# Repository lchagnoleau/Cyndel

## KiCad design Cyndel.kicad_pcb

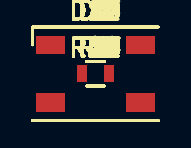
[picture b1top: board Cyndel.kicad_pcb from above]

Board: 2 copper layers, 80 parts (0 on the bottom side), 91 nets, no tracks yet.

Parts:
D1, D2, D3, D4, D5, D6, D7, D8, D9, D10, D11, D12, D13, D14, D15, D16, D17, D18, D19, D20: LED_RABG; LED_Cree-PLCC4
R1, R2, R3, R4, R5, R6, R7, R8, R9, R10, R11, R12, R13, R14, R15, R16, R17, R18, R19, R20, R21, R22, R23, R24, R25, R26, R27, R28, R29, R30, R31, R32, R33, R34, R35, R36, R37, R38, R39, R40, R41, R42, R43, R44, R45, R46, R47, R48, R49, R50, R51, R52, R53, R54, R55, R56, R57, R58, R59, R60: 220R; R_0603

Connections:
/B1: R3.2, R33.2
/B2: R6.2, R36.2
/B3: R9.2, R39.2
/B4: R12.2, R42.2
/B5: R15.2, R45.2
/B6: R18.2, R48.2
/B7: R21.2, R51.2
/B8: R24.2, R54.2
/B9: R27.2, R57.2
/B10: R30.2, R60.2
/G1: R2.2, R32.2
/G2: R5.2, R35.2
/G3: R8.2, R38.2
/G4: R11.2, R41.2
/G5: R14.2, R44.2
/G6: R17.2, R47.2
/G7: R20.2, R50.2
/G8: R23.2, R53.2
/G9: R26.2, R56.2
/G10: R29.2, R59.2
/R1: R1.2, R31.2
/R2: R4.2, R34.2
/R3: R7.2, R37.2
/R4: R10.2, R40.2
/R5: R13.2, R43.2
/R6: R16.2, R46.2
/R7: R19.2, R49.2
/R8: R22.2, R52.2
/R9: R25.2, R55.2
/R10: R28.2, R58.2
unnamed: D1.1, R1.1
unnamed: D1.3, R3.1
unnamed: D1.4, R2.1
unnamed: D2.1, R4.1
unnamed: D2.3, R6.1
unnamed: D2.4, R5.1
unnamed: D3.1, R7.1
unnamed: D3.3, R9.1
unnamed: D3.4, R8.1
unnamed: D4.1, R10.1
unnamed: D4.3, R12.1
unnamed: D4.4, R11.1
unnamed: D5.1, R13.1
unnamed: D5.3, R15.1
unnamed: D5.4, R14.1
unnamed: D6.1, R16.1
unnamed: D6.3, R18.1
unnamed: D6.4, R17.1
unnamed: D7.1, R19.1
unnamed: D7.3, R21.1
unnamed: D7.4, R20.1
unnamed: D8.1, R22.1
unnamed: D8.3, R24.1
unnamed: D8.4, R23.1
unnamed: D9.1, R25.1
unnamed: D9.3, R27.1
unnamed: D9.4, R26.1
unnamed: D10.1, R28.1
unnamed: D10.3, R30.1
unnamed: D10.4, R29.1
unnamed: D11.1, R31.1
unnamed: D11.3, R33.1
unnamed: D11.4, R32.1
unnamed: D12.1, R34.1
unnamed: D12.3, R36.1
unnamed: D12.4, R35.1
unnamed: D13.1, R37.1
unnamed: D13.3, R39.1
unnamed: D13.4, R38.1
unnamed: D14.1, R40.1
unnamed: D14.3, R42.1
unnamed: D14.4, R41.1
unnamed: D15.1, R43.1
unnamed: D15.3, R45.1
unnamed: D15.4, R44.1
unnamed: D16.1, R46.1
unnamed: D16.3, R48.1
unnamed: D16.4, R47.1
unnamed: D17.1, R49.1
unnamed: D17.3, R51.1
unnamed: D17.4, R50.1
unnamed: D18.1, R52.1
unnamed: D18.3, R54.1
unnamed: D18.4, R53.1
unnamed: D19.1, R55.1
unnamed: D19.3, R57.1
unnamed: D19.4, R56.1
unnamed: D20.1, R58.1
unnamed: D20.3, R60.1
unnamed: D20.4, R59.1
VDD: D1.2, D2.2, D3.2, D4.2, D5.2, D6.2, D7.2, D8.2, D9.2, D10.2, D11.2, D12.2, D13.2, D14.2, D15.2, D16.2, D17.2, D18.2, D19.2, D20.2

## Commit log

2017-10-02 add files
2017-10-02 update gitignore
2017-10-03 add LED network and power
2017-10-04 saving work
